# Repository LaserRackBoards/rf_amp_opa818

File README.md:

# rf_amp_opa818
Triple general purpose rf amplifier board based on OPA818 with BUF602 output-buffer.

Predicted gain and bandwith from OPA818 datasheet:

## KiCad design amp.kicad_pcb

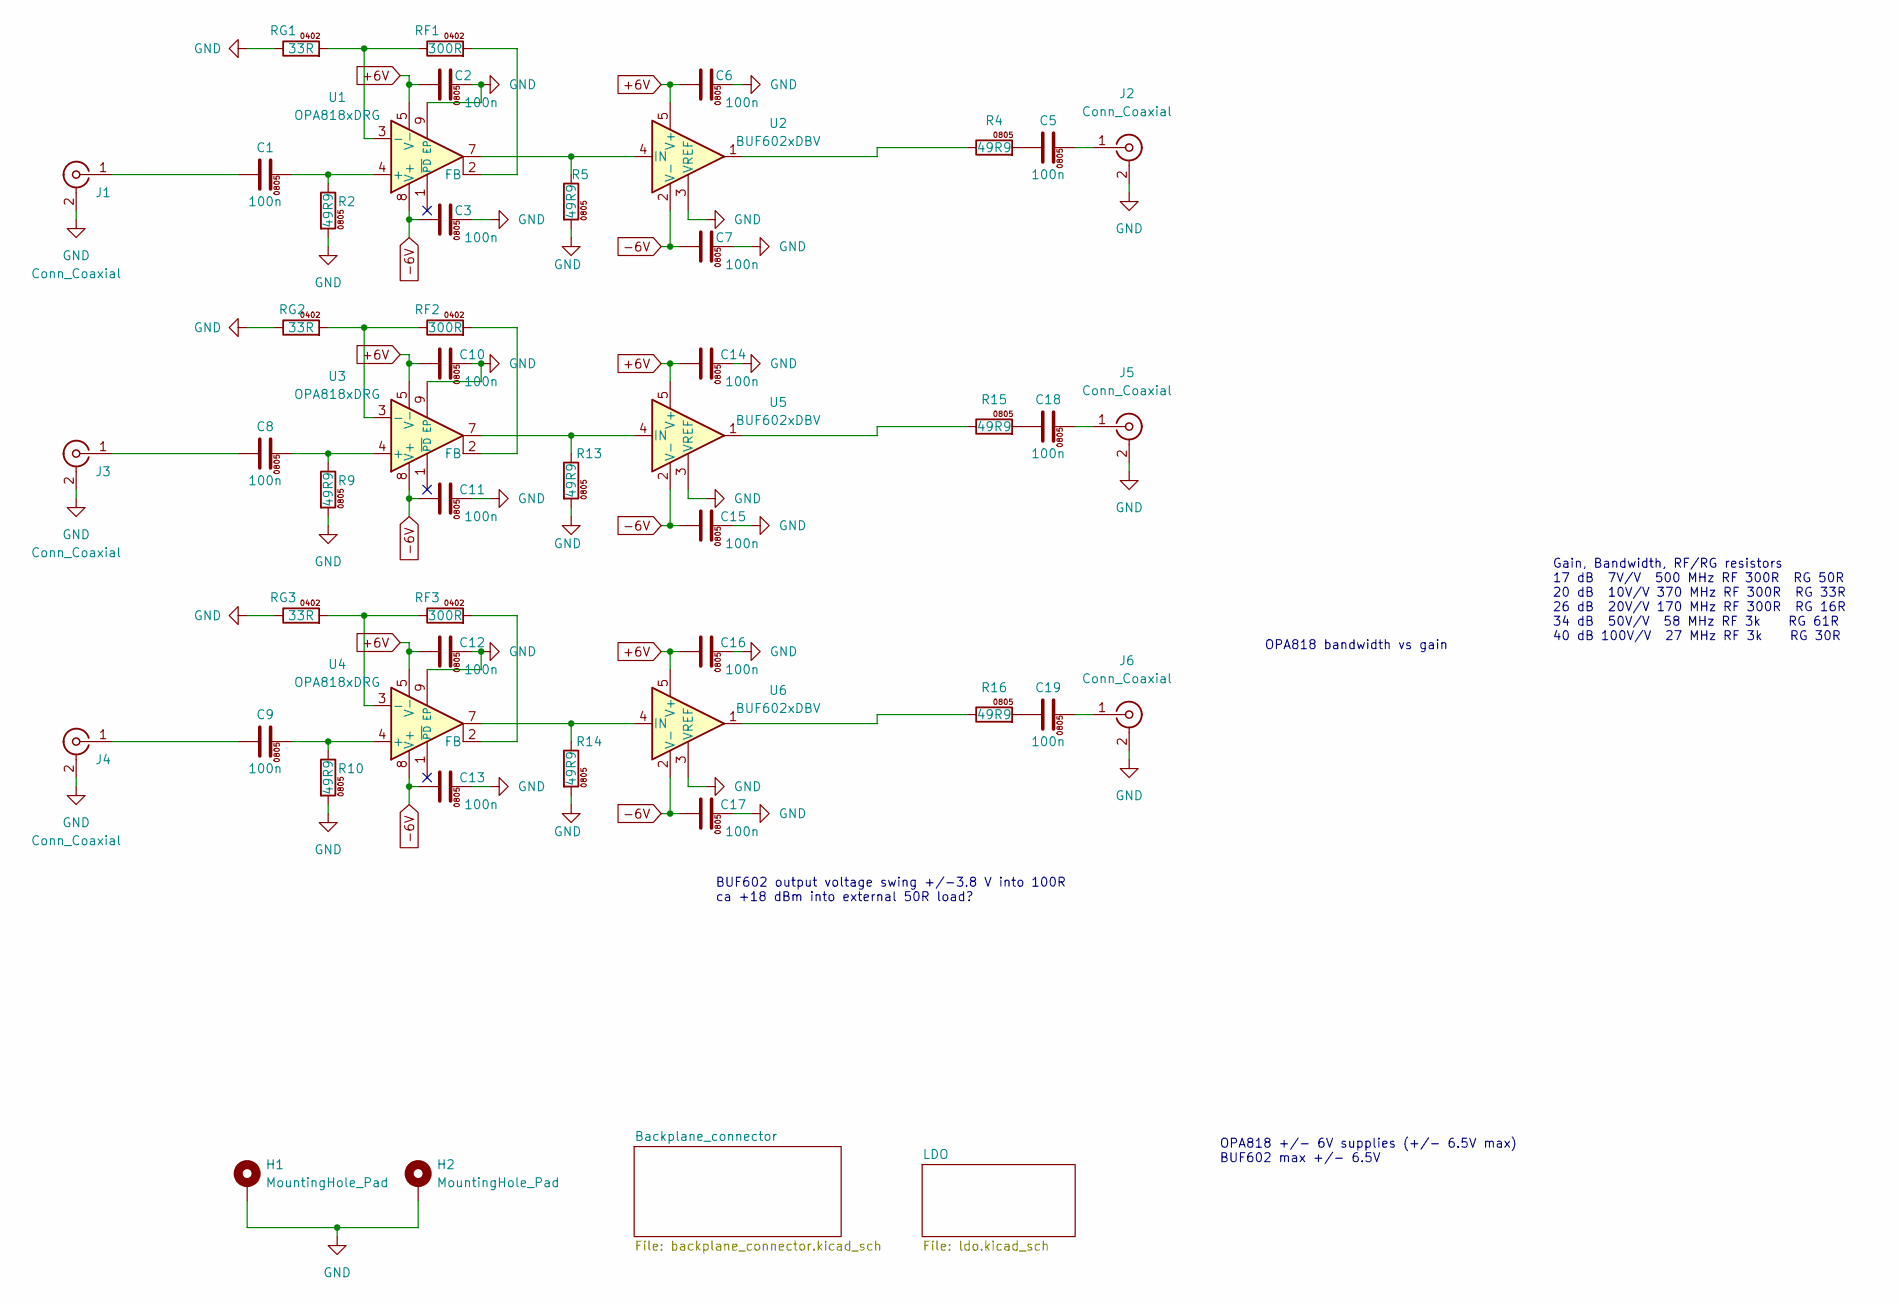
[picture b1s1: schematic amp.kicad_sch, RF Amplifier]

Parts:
C1, C2, C3, C5, C6, C7, C8, C9, C10, C11, C12, C13, C14, C15, C16, C17, C18, C19: 100n; C_0805_2012Metric
H1, H2: MountingHole_Pad; MountingHole_2.7mm_M2.5_DIN965_Pad
J1, J2, J3, J4, J5, J6: Conn_Coaxial; SMA_Amphenol_132203-12_Horizontal
R2, R4, R5, R9, R10, R13, R14, R15, R16: 49R9; R_0805_2012Metric
RF1, RF2, RF3: 300R; R_0402_1005Metric
RG1, RG2, RG3: 33R; R_0402_1005Metric
U1, U3, U4: OPA818xDRG; WSON-8-1EP_3x3mm_P0.5mm_EP1.45x2.4mm
U2, U5, U6: BUF602xDBV; SOT-23-5

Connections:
GND: C2.2, C3.2, C6.2, C7.2, C10.2, C11.2, C12.2, C13.2, C14.2, C15.2, C16.2, C17.2, H1.1, H2.1, J1.2 (Ext), J2.2 (Ext), J3.2 (Ext), J4.2 (Ext), J5.2 (Ext), J6.2 (Ext), R2.2, R5.2, R9.2, R10.2, R13.2, R14.2, RG1.1, RG2.1, RG3.1, U1.9 (EP), U2.3 (VREF), U3.9 (EP), U4.9 (EP), U5.3 (VREF), U6.3 (VREF); also elsewhere on the board
unnamed: C1.1, J1.1 (In)
unnamed: C1.2, R2.1, U1.4 (+)
unnamed: C5.1, R4.2
unnamed: C5.2, J2.1 (In)
unnamed: C8.1, J3.1 (In)
unnamed: C8.2, R9.1, U3.4 (+)
unnamed: C9.1, J4.1 (In)
unnamed: C9.2, R10.1, U4.4 (+)
unnamed: C18.1, R15.2
unnamed: C18.2, J5.1 (In)
unnamed: C19.1, R16.2
unnamed: C19.2, J6.1 (In)
unnamed: R4.1, U2.1
unnamed: R5.1, U1.7, U2.4 (IN)
unnamed: R13.1, U3.7, U5.4 (IN)
unnamed: R14.1, U4.7, U6.4 (IN)
unnamed: R15.1, U5.1
unnamed: R16.1, U6.1
unnamed: RF1.2, U1.2 (FB)
unnamed: RF2.1, RG2.2, U3.3 (-)
unnamed: RF2.2, U3.2 (FB)
unnamed: RF3.1, RG3.2, U4.3 (-)
unnamed: RF3.2, U4.2 (FB)
unnamed: RF1.1, RG1.2, U1.3 (-)

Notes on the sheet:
OPA818 bandwidth vs gain
OPA818 +/- 6V supplies (+/- 6.5V max) BUF602 max +/- 6.5V
Gain, Bandwidth, RF/RG resistors 17 dB 7V/V 500 MHz RF 300R RG 50R 20 dB 10V/V 370 MHz RF 300R RG 33R 26 dB 20V/V 170 MHz RF 300R RG 16R 34 dB 50V/V 58 MHz RF 3k RG 61R 40 dB 100V/V 27 MHz RF 3k RG 30R
BUF602 output voltage swing +/-3.8 V into 100R ca +18 dBm into external 50R load?

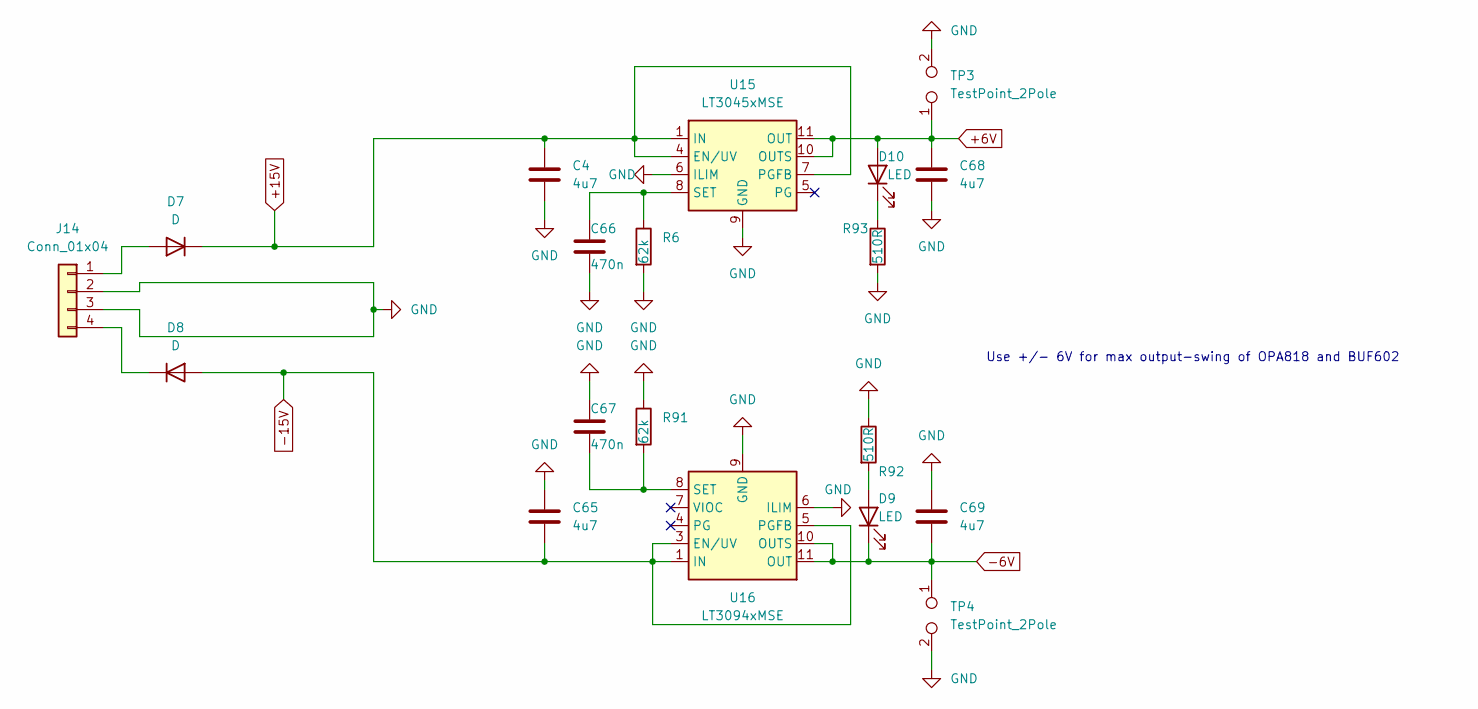
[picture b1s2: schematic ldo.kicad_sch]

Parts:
C4, C65, C68, C69: 4u7; C_0805_2012Metric
C66, C67: 470n; C_0805_2012Metric
D7, D8: D; D_SMB
D9, D10: LED; LED_0805_2012Metric
J14: Conn_01x04; TerminalBlock_TE_282834-4_1x04_P2.54mm_Horizontal
R6, R91: 62k; R_0805_2012Metric
R92, R93: 510R; R_0805_2012Metric
TP3, TP4: TestPoint_2Pole; TestPoint_2Pads_Pitch2.54mm_Drill0.8mm
U15: LT3045xMSE; MSOP-12-1EP_3x4mm_P0.65mm_EP1.65x2.85mm
U16: LT3094xMSE; MSOP-12-1EP_3x4mm_P0.65mm_EP1.65x2.85mm

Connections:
+15V: C4.1, D7.1 (K), U15.1 (IN), U15.2 (IN), U15.3 (IN), U15.4 (EN/UV), U15.7 (PGFB); also elsewhere on the board
-15V: C65.2, D8.2 (A), U16.1 (IN), U16.2 (IN), U16.3 (EN/UV), U16.5 (PGFB), U16.13 (IN); also elsewhere on the board
GND: C4.2, C65.1, C66.2, C67.1, C68.2, C69.1, J14.2, J14.3, R6.2, R91.1, R92.1, R93.2, TP3.2, TP4.2, U15.6 (ILIM), U15.9 (GND), U15.13 (GND), U16.6 (ILIM), U16.9 (GND); also elsewhere on the board
unnamed: C66.1, R6.1, U15.8 (SET)
unnamed: C67.2, R91.2, U16.8 (SET)
unnamed: D7.2 (A), J14.1
unnamed: D8.1 (K), J14.4
unnamed: D9.2 (A), R92.2
unnamed: D10.1 (K), R93.1

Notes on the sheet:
Use +/- 6V for max output-swing of OPA818 and BUF602

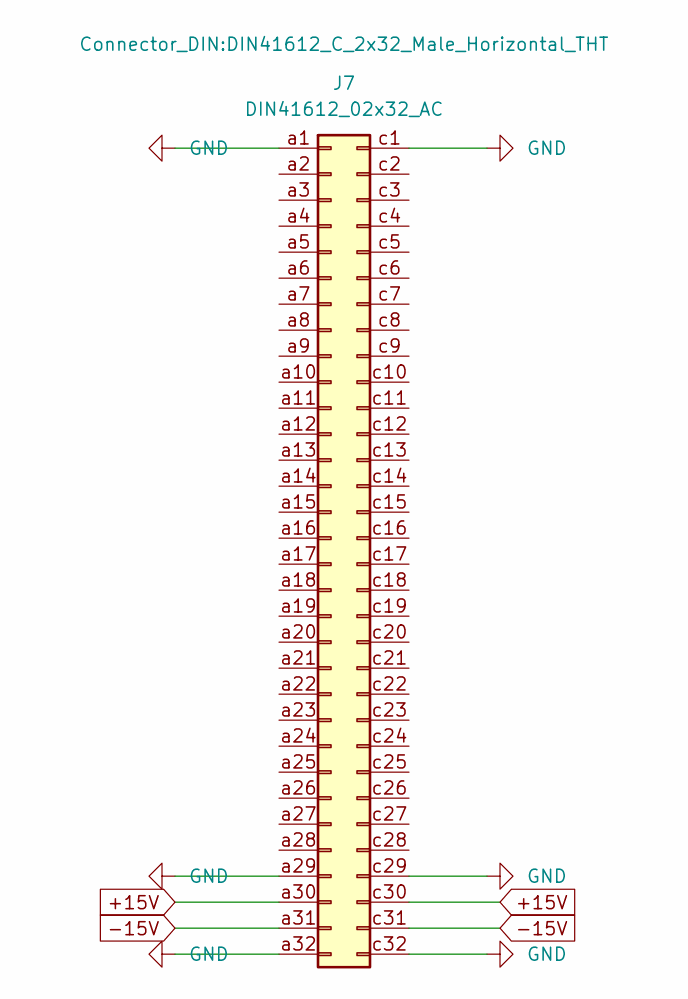
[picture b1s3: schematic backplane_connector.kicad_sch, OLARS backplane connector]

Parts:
J7: DIN41612_02x32_AC; DIN41612_C_2x32_Male_Horizontal_THT

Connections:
+15V: J7.a30, J7.c30; also elsewhere on the board
-15V: J7.a31, J7.c31; also elsewhere on the board
GND: J7.a1, J7.a29, J7.a32, J7.c1, J7.c29, J7.c32; also elsewhere on the board

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
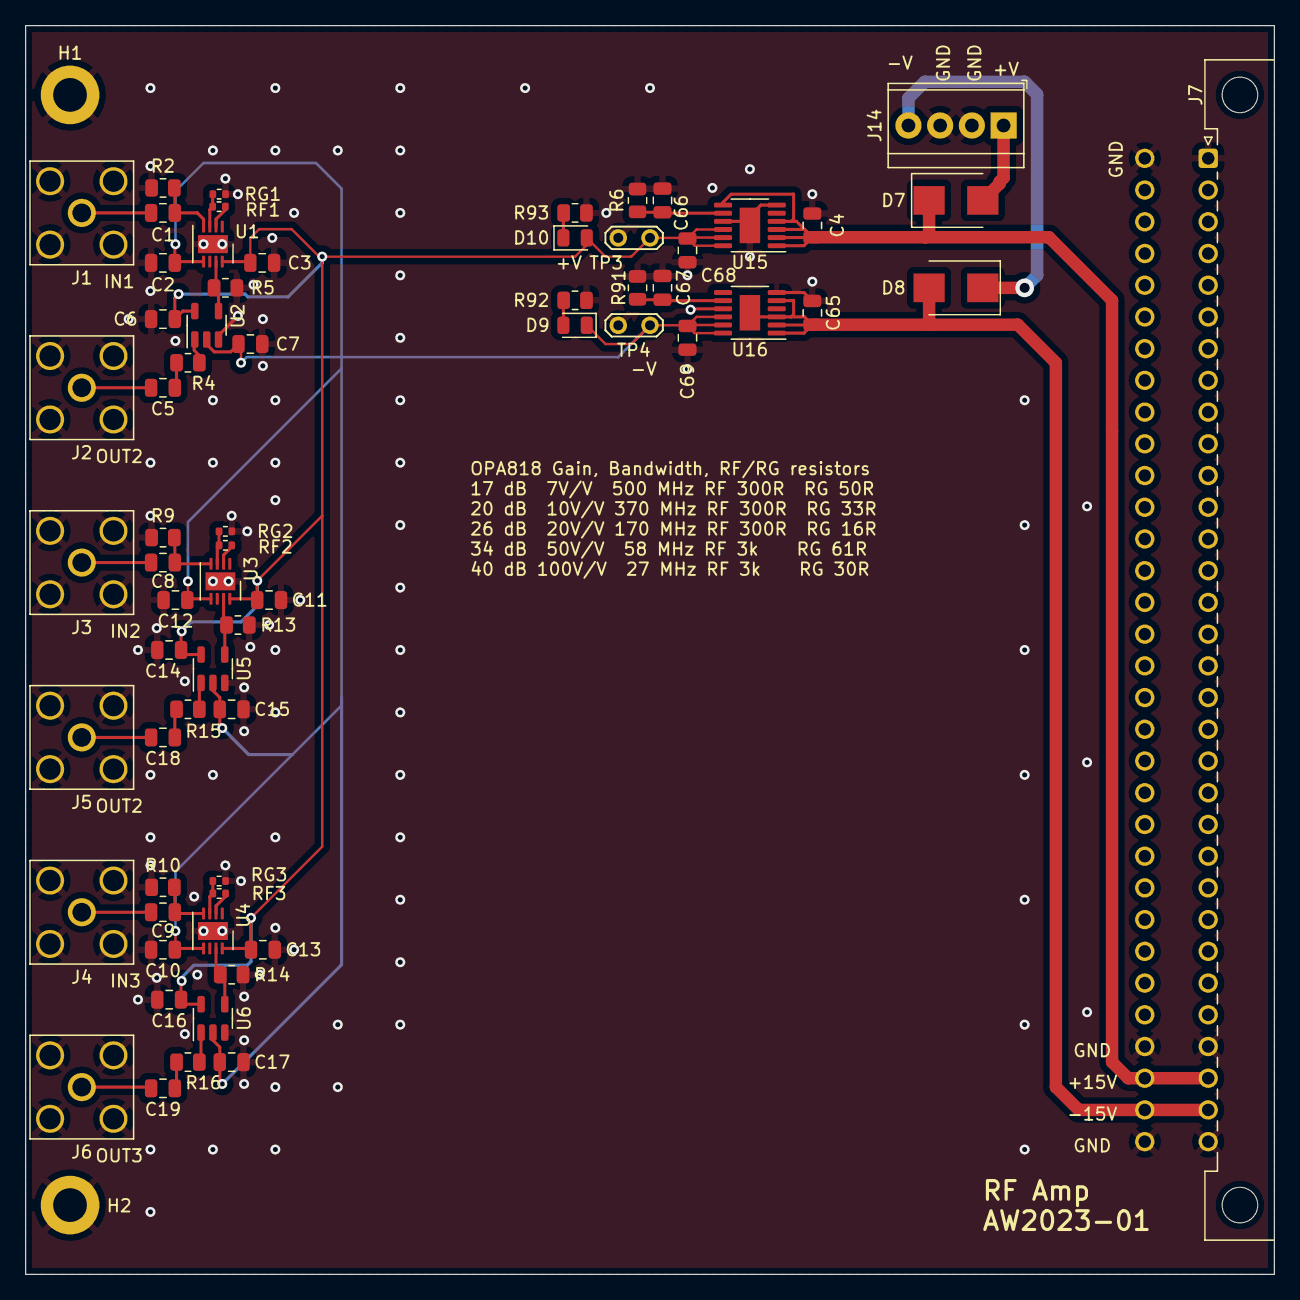
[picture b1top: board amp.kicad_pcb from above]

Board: 2 copper layers, 100.0 x 100.0 mm, 67 parts (0 on the bottom side), 35 nets.
